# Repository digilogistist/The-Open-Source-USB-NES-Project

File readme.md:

# USB-NES Lite Project Public Release

Brad Taylor  
BTTD Group  
04/05/2023  
https://usbnes.com  

### This is the complete USB-NES Lite 0.08/0.79 production unit engineering archive, containing:

- Source code
- Firmware binaries (composite and discrete)
- PCB engineering files (USB-NES, NES-BACKUP and new NES-FASTGFX)
- Serial wire debug wiring diagram
- Technical documentations
- Quick setup guide print-out
- DIY kit guide print-out (manufacturing instructions)
- Owner's manual PDF
- 3D case models
- Manufacturing BOMs and part source links
- Photo gallery

## Firmware Binaries

Inside the USB-NES is an STM32F103C8 microcontroller running at 72 MHz, which usually includes a very cozy 64 K Bytes of on-board flash memory.  Sometimes as a bonus though, the "Blue Pill" comes with double that amount of storage (and possibly even all the time).  While these differences are normally considered a toss-up on a few innocent chance purchases, the 128 KB flash types (aka incognito 'F103CB ones) are more commonly seen with marketplace Blue Pill system boards at slightly higher price points.

Nowadays, the Blue Pills are not as cheap, available, nor as powerful as newer mini system board offerings on the market, but the first generation blue pills with the through-hole mounted micro-USB port and low-profile reset push button switches are the absolute best types you can still get your hands on, if you're lucky.

Moreover, the main functional USB-NES firmware uses only the first 64 KB of flash, where as units with 128 KB would include a DEMO.NES graphics demonstration ROM that would fit in the bonus 64 KB of flash as additional superfluous brand marketing.  The firmware checks for the classic iNES signature where the DEMO.NES file is allocated on the flash to determine if the file should be created in the USB-NES file system.  Therefore, the DEMO.NES binary allocated there can technically be any defacto .NES image that can fit within the high 64 KB flash of a lucky 128 KB Blue Pill sample.  

|Micro Type  |Flash Location|Size  |Composite Binary Source         |
|:-----------|-------------:|-----:|:-------------------------------|
|STM32F103C8 |0x 0800 0000  | 64 KB|/USB-NES_Lite_0.08-0.79_64K.bin |
|STM32F103CB~|0x 0800 0000  |128 KB|/USB-NES_Lite_0.08-0.79_128K.bin|

~ may also be labelled as a "lucky" 'F103C8 model.  

|Flash section |Flash Location|Size |Discrete Binary Location                   |
|:-------------|-------------:|----:|:------------------------------------------|
|Boot Block   @|0x 0800 0000  | 4 KB|/firmware/boot_block/boot_block.bin        |
|Kernel      ~$|0x 0800 1000  |28 KB|/firmware/kernel/Debug/kernel.bin          |
|Application ^$|0x 0800 8000  |26 KB|/firmware/application/Debug/application.bin|
|SETTINGS.TXT %|0x 0800 E800  | 1 KB|                                           |
|BCMTABLE.BIN  |0x 0800 EC00  | 1 KB|/firmware/BCMTABLE.BIN                     |
|OVERRIDE.BIN  |0x 0800 F000  | 4 KB|/firmware/OVERRIDE.BIN                     |
|DEMO.NES     &|0x 0801 0000  |64 KB|/firmware/DEMO.BIN                         |

~ Uses lower 10 KB of system RAM  
^ Uses upper 10 KB of system RAM  
$ Compiled using Atollic TruStudio (see ./BUILD.BAT for console log)  
% This data is auto-generated by the application firmware  
& DEMO.NES is disabled in SETTINGS.TXT by default  
@ Assembled and output to binary using windy script /firmware/boot_block/BUILD.BAT  

### Flashing the discrete binaries to USB-NES
1. Acquire an ST-LINK Serial Wire Debug programming tool; they are cheap + easy to get.
2. Install the ST-LINK programming utility software.
3. Refer to the /USB-NES-SWD_pinout.jpg for connecting the ST-LINK to USB-NES via SWD.
4. Be sure the USB-NES has its USB port powered when connecting via SWD.
5. Hold in the reset button on USB-NES for a couple of seconds or so, while using the ST-LINK utility to connect to the STM32F103 micro via SWD interface.
6. Deactivate the readout protection on the STM32F103 by unchecking it in the option switches.  Please note this will completely erase the existing contents of the USB-NES firmware.  If the readout protection is not active, you should instead erase the entire contents of the chip by using the utility's Erase command.
7. Load the binary files into the ST-LINK utility~, and program them to the aforementioned corresponding locations in flash memory.  The five critical binaries to flash to USB-NES are the Boot Block, Kernel, Application, BCMTABLE.BIN, and OVERRIDE.BIN.  SETTINGS.TXT is auto-generated by the application, and DEMO.NES is entirely optional (for 128 KB units only).

~ Alternately, the ST-LINK utility command line interface may also be used to flash all five critical binaries automatically; please see /FLASHBALL.BAT for a windy example.

## Source Code

The Kernel and Application projects offered here are built with STM32cubeMX, using the USB FS and mass storage class middlewares provided by ST Microelectronics, which is copywritten code.  Therefore, their source code is provided here strictly under the "fair use" doctrine; no infringement is implied nor intended in its parallel inclusion with this public-domain USB-NES preservation project and related functional source code files.

This default USB layer uses almost all the flash space in the kernel, but probably can be optimized to use less.  Moreover, the STM32cubeMX does not allow the implementation of a USB composite device (such as MSC + HID) on this particular STM32 micro; this is why USB-NES Lite never got NES gamepad socket add-ons over its trial run.  Many on-and-off attempts were made to hack together the two separate STM32 USB functions with no success; it is not clear to me at the time of this writing if the STM32F103C8 has enough flash or RAM resources to employ a USB MSC + HID composite device within the confines of the kernel binary.

The main functional USB-NES source code provided here is located as follows:

|Source type|Language  |Size  |Location                              |
|:----------|:---------|-----:|:-------------------------------------|
|Boot Block |ARM M3 ASM| 13745|/firmware/boot_block/boot_block.s     |
|Kernel     |C         | 25177|/firmware/kernel/Src/usbd_storage_if.c|
|Application|C         |120352|/firmware/application/Src/main.c      |

## PCB Files

Both USB-NES-02 and NES-BACKUP-02 are electrically identical products, and differ only with the Blue Pill/USB port orientation (side vs. back) to their respective PCBs.

The NES-BACKUP-02 PCB predates USB-NES-02, and does not have a nice shell design like for USB-NES Lite.  Note the only feature of this PCB is the 6-pin header that connects to the NES cartridge CIC pins, for easy AVR CIclone boardset programming.  Only 11 NES-BACKUP-01 units are currently known to exist.  Note there is no corner mounting holes, nor is there a footprint for the necessary electrolytic capacitor in this design, which are bugs that need addressing.  The -02 revision fixes a footprint pinout bug present on the -01 models, involving the orientation of the power MOSFET component.

USB-NES-02 is a better follow-up PCB to the aforementioned design, that adds in an experimental mini phone plug for theoretical expansion audio access, and leaves room in the front for further possible expansions like NES gamepad ports and such.  At least 100 USB-NES-01 PCB assemblies are known to exist, and many of these have been assembled into complete USB-NES Lite consumer units.  Note there is no footprint for the necessary electrolytic capacitor in this design, but it is possible to piggy-back solder it onto existing points on the PCB assembly (see /cap_add/ for pix).  A 1.6 mm PCB thickness is strongly recommended for manufacturing USB-NES-02.  All USB-NES firmware binaries mentioned in this document are intended for USB-NES-02.

USB-NES-04 is an enhanced version of the previous design that adds four controller ports to the USB-NES.  There is no firmware that exists yet to take advantage of the enhancements in this hardware design.  Moreover, no PCBs nor related shell designs have yet been manufactured for this either.  More info here:  
https://youtu.be/dRpi10Yrjks

NES-FASTGFX-01 is a completely original concept NES cart mapper (1.2 mm thick) PCB design made for new NES game development.  A complete manufacturing BOM + working (as of 04-13-2023) parts source list for NES-FASTGFX-01 can be found in "/PCB (NES-FASTGFX-01)/BOM-FASTGFX.ods"

### NES-FASTGFX-01 Specs
- 512 K byte PRG flash (SST39SF040)
- 32 K byte PRG-RAM
- 512 K byte CHR-RAM
- 32768 playfield tiles (@ PPU $0000-$0FFF)
- 4 PPU mirroring modes
- 16-bit VBLANK time stamp counter
- 128 sprite banks (@ PPU $1000-$1FFF)
- HI name table located in first 2 KB of CHR-RAM
- 4-CPU clock cycle CHR-RAM byte filling @ PPU $2000-$3EFF~
- ATMEL ATtiny13A CIClone twin footprint (through-hole & SMT)

~ CPU writes to PPU data I/O register $2xx7/$3xx7, will write the encoded 8-bit xx value to the CHR-RAM in one single STA/STX/STY abs. 6502 instruction.  In this case, writes to PPU $2000-$2FFF memory will fill the HI name tables with the xx value (and internal 2 KB LO NT as per usual CPU data), while writes to PPU $3000-$3EFF will write xx to the selected CHR-RAM sprite bank (meanwhile disabling the LO NT).  The CHR-RAM may also be disabled during name table fills, when updating only the LO NT is desired.   Moreover, the CHR-RAM may also be bi-directionally accessed via the traditional CPU $2007 data I/O port @ PPU $1000-$1FFF memory, swapping in the selected 4 KB sprite bank there as well.  PPU bank $0000-$0FFF is only used for playfield rendering; it can just be ignored otherwise.

The most notable feature of this mapper is the expansion of the original 8-bit name table tile codes to 15-bits; this is made possible by using a private graphics data bus in the cartridge for handling the NT HI business during a NT fetch phase.  Moreover, the NT fetch phase is identified as a read cycle from PPU $2000-$3FFF that follows a read from PPU $0000-$1FFF; this corresponds to how the PPU fetches CHR memory during on-screen playfield rendering.  The NT HI byte is then fetched from the first 2KB of CHR-RAM (using the identical mirroring scheme the NES internal 2K VRAM is configured for), and is stored in a register.  The register is then used as the basis for the 4KB bank selection for pattern graphics access @ PPU $0000-$0FFF, which is where the PPU should be normally configured to allocate the 4KB playfield graphics bank.

The VBLANK time stamp counter is reset from any reads from the PPU, so once screen rendering is done, this counter will start to count up every CPU clock.  Consequently, the 16-bit value read here can indicate how far the PPU is in VBLANK or the frame render period, relative to the CPU NMI event (or thereabouts).  If your VBLANK code runs past the 20-scanline (NTSC) limit, the time stamp counter can be used as the basis for forming the correct PPU scroll programming values, based on how many scanlines the render has advanced into the visible frame.  Reading the LO byte of the time stamp count register latches the next LO and HI 8-bit time stamp count samples to be read back.  Therefore, it is possible to only just read the LO TSC register when measuring CPU clock counts of less than 256 clocks.

When using FASTGFX for NES game development, writing to PPU memory is up to 50% faster, and VBLANK code time may be extended dynamically past the on-screen cutoff point, all while having access to a serious amount of graphical tiles for use with both backgrounds and sprites.

### Flash Cart Story
NES-FASTGFX-01 is the answer to a previous programmable NES cart production attempt I made back in 2018: "NES-RED-PILL-02". This older design was more complicated due to the presence of both CHR-RAM and CHR-flash, where the PPU architecture is split into separate sections for sprites (RAM) and playfield tiles (flash/RAM).  The idea was to have 512 KB of CHR-flash for background tiles, and 32 KB CHR-RAM for sprites + BG, but the hardware required to implement the 16-bit background tile index code extensions ended up making programming the CHR-flash chip a complex nightmare.

This was also my first attempt implementing 5-volt flash chips into a new NES cart design.  One critical detail about using flash chips for PRG memory versus SRAM is the requirement of an inverted read/write line for the /OE input on the chip, which would normally just be tied to ground for a typical SRAM implementation.

My long-term plan was to develop game software for the NES using these cart boards, while using NES-BACKUP/USB-NES as the main flashing/programming tool, providing an easy-to-use drag + drop user interface.  These boards have a lot of SMD parts on them, so I got ten of them manufactured and populated professionally, which also made this cart production really expensive.

Subsequently however, once I had built NES-BACKUP and started testing out the NES-RED-PILL boards, I found out I made some fatal design mistakes on the boards.  Most notably, I discovered that both CHR and PRG flash chips could not be programmed efficiently or even at all, without reworking the boards and adding another chip!  After eventually reworking one board, I did manage to get the PRG + CHR flashing to work with USB-NES, but when programming the CHR-flash there was always 4KB in the last bank on the chip that would not flash correctly.  I couldn't figure out what the source of the CHR-flash corruption was, and lost my nerve.  From there on (late 2019), I focused on developing the USB-NES firmware, since I was at a loss with my game boards.

Then three years later, I reworked a second NES-RED-PILL board to discover that the CHR-flash on the first board was actually fried.  Apparently, all the initial testing I was doing on these boards before reworking them was enough to cause the CHR-flash chip on one board to partially self-destruct, and cause it to always fail a full flash memory programming test.  But now, the second reworked board was flashing perfectly using USB-NES!  So now I know what I did wrong, and how to do it right this time.

I took everything I learned from that first costly and disappointing NES-RED-PILL production disaster, trimmed the fat and tweaked the ideas, and made NES-FASTGFX: a state-of-the-art, open-source, graphics expansion NES development cartridge boardset PCB design, that adds powerful extensions to the NES architecture with a simplified programming environment, using a handful of easy-to-source boardset parts.

USB-NES support for NES-FASTGFX boardset development with full drag + drop PRG-flashing is speculated down the road, using existing methods in the USB-NES source code that have been 100% tested and confirmed working on reworked NES-RED-PILL-02 flash boards.  More info on the NES-RED-PILL can be seen here:

https://youtu.be/C34mVn180Tk  
https://youtu.be/JX10NZo6VX4

## USB-NES Lite BOM

/BOM-final_USB-NES_Lite_2021.ods

This bill of materials includes everything to make a production USB-NES Lite system, with a working (as of 04-13-2023) part source list.

The 3D models are typically printed via 1.75/0.4 mm filament/nozzle 3D printer with 5% infill, 0.2 mm layers, and 1.2 mm top/bottom thickness.

The PCB files were made with Kicad.

Do not assemble before reading the manufacturing instructions.

## Manufacturing Instructions

The step-by-step assembly guide for building USB-NES Lite is contained in:  
/USB-NES DIY KIT (p.1).pdf  
/USB-NES DIY KIT (p.2).pdf  
https://usbnes.com/usb-nes-lite-diy-kit/  

The companion video can be found here (doesn't cover adding the capacitor):  
https://youtu.be/VL_1Z1ONgns  

The capacitor install guide here:  
/cap_add/  
https://usbnes.com/power-system-upgrade/

## Thank-Yous

All the USB-NES Lite project supporters  
The entire NES emulation dev scene  
Generational Gamer  
Paul Belanger  
Thor Robinson  
Troy Denton  
Henry Hoy  
Wolf  
Loopy  
Disch  
Dwedit  
Blarrg  
nocash  
Tepples  
Kevtris  
Bootgod  
Bregalad  
Bananmos  
Tokumaru  
Lidnariq  
Ulfalizer  
Rainwarrior  
infiniteneslives  
beannaich  
Quietust  
Memblers  
jeffqchen  
NEScartDB  
NESDEV wiki  
Eugene's blog  
ST Microelectronics  
Nintendo of America, Inc. (and NCL of Japan, too)  
And of course, the reader  

## License

Copywritten works, such as technical manuals and source code included in this repository are for educational and preservational "fair use" purposes only.  No copyright infringement is implied, solicited nor intended with the inclusion of these copywritten works for the Open-Source USB-NES Project.

The rest of the work in this archive, including any BTTD Group or Brad Taylor properties, is licensed under a Creative Commons Attribution-ShareAlike 4.0 International License.

http://creativecommons.org/licenses/by-sa/4.0/

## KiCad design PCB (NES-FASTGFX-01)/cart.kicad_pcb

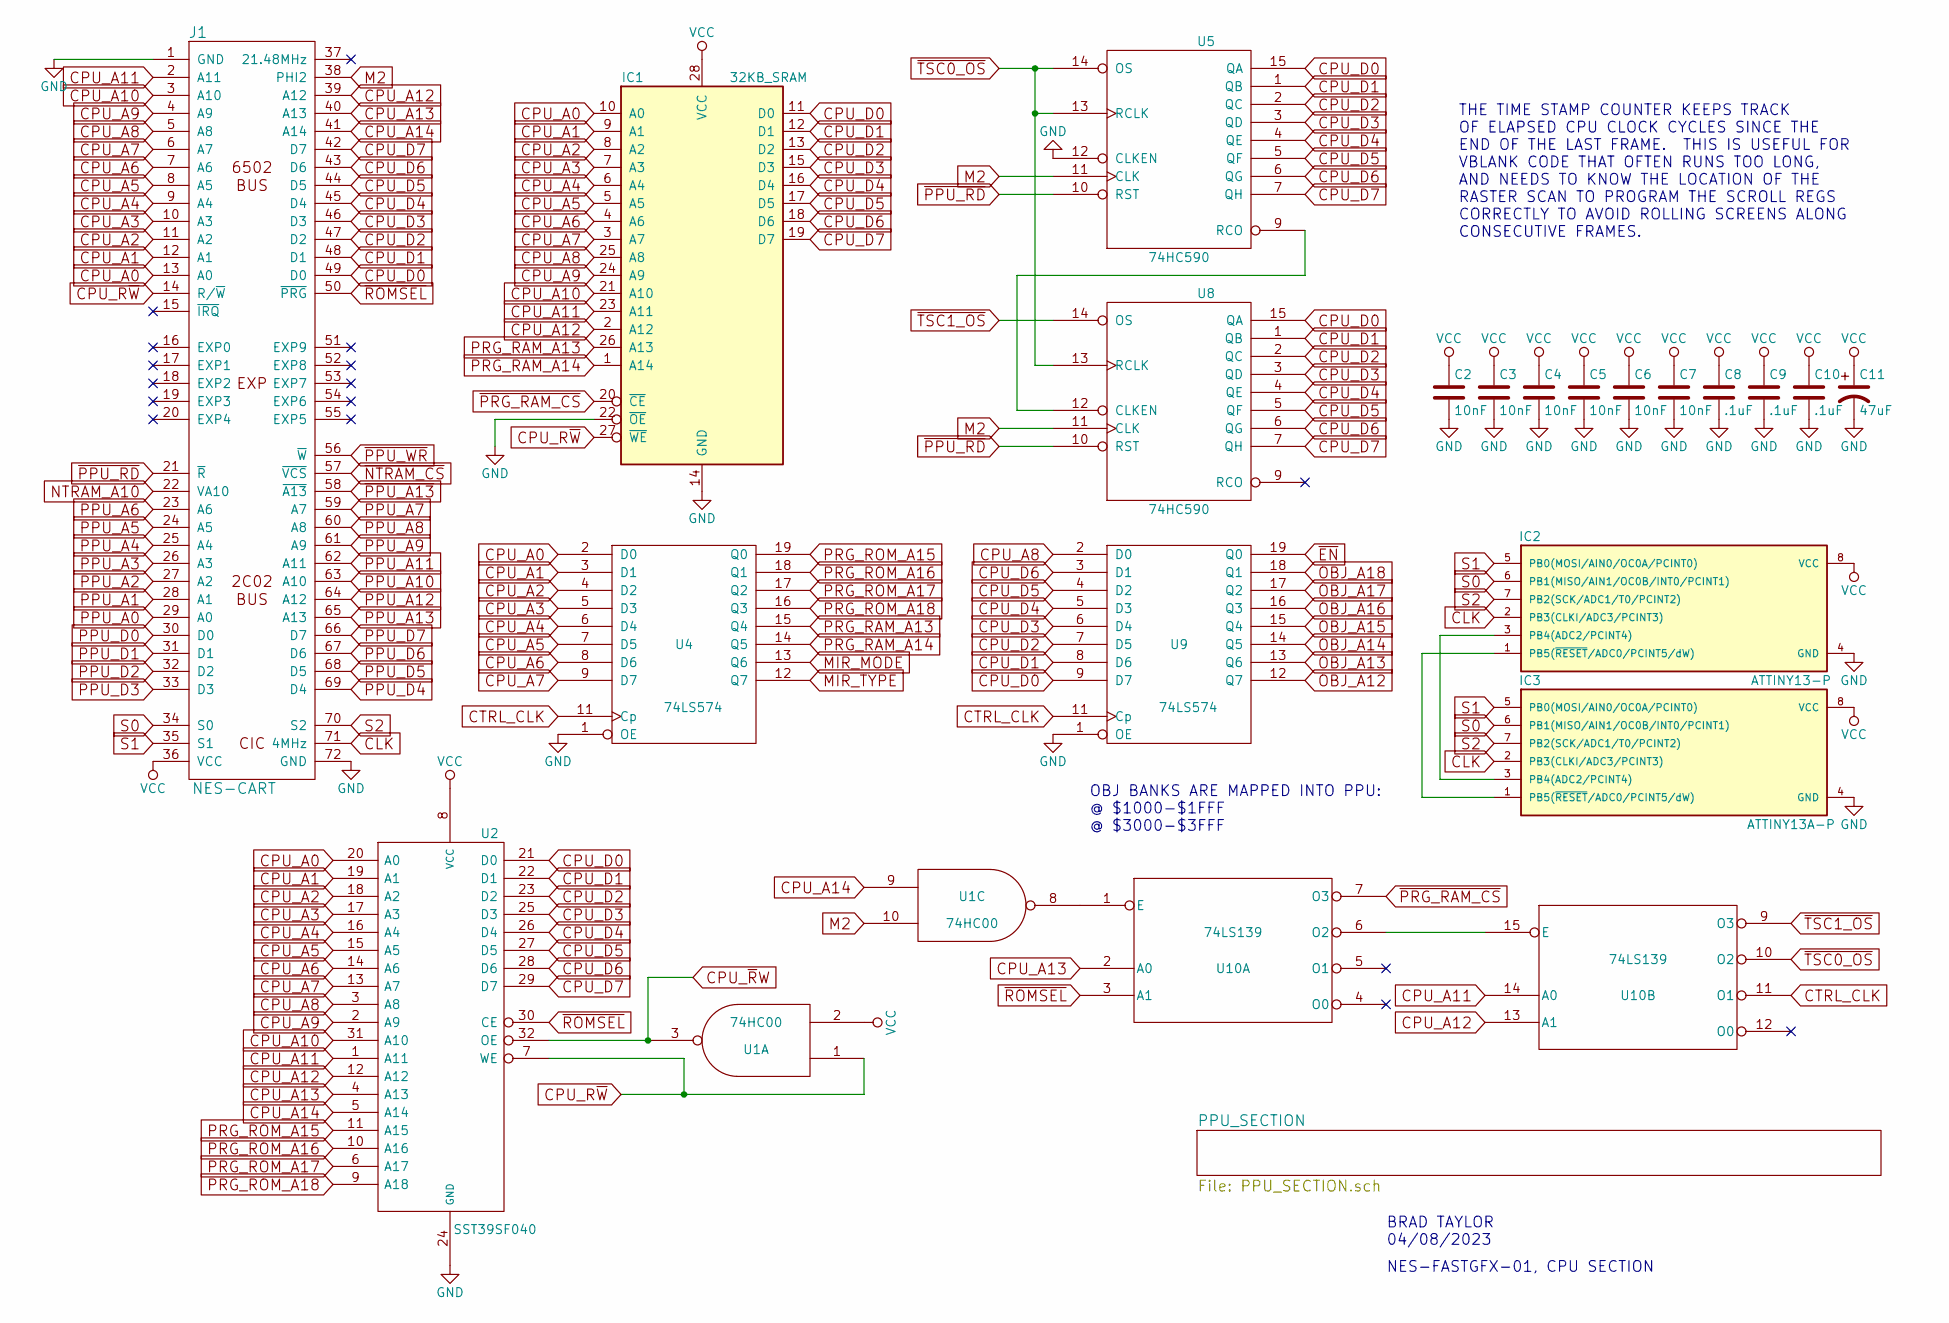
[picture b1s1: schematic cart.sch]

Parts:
C2, C3, C4, C5, C6, C7: 10nF; C_0603_1608Metric_Pad1.05x0.95mm_HandSolder
C8, C9, C10: .1uF; C_0603_1608Metric_Pad1.05x0.95mm_HandSolder
C11: 47uF; CP_Elec_4x5.3
IC1: 32KB_SRAM; SOIC-28
IC2: ATTINY13-P; DIP-8_W7.62mm
IC3: ATTINY13A-P; SOIC-8_3.9x4.9mm_P1.27mm
J1: NES-CART; NES_CART_FINGERS
U1: 74HC00; TSSOP-14_4.4x5mm_P0.65mm
U2: SST39SF040; SOIC-32
U4, U9: 74LS574; TSSOP-20_4.4x6.5mm_P0.65mm
U5, U8: 74HC590; TSSOP-16_4.4x5mm_P0.65mm
U10: 74LS139; TSSOP-16_4.4x5mm_P0.65mm

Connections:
CLK: IC2.2 (PB3(CLKI/ADC3/PCINT3)), IC3.2 (PB3(CLKI/ADC3/PCINT3)), J1.71 (4MHz)
CPU_A0: IC1.10 (A0), J1.13 (A0), U2.20 (A0), U4.2 (D0)
CPU_A1: IC1.9 (A1), J1.12 (A1), U2.19 (A1), U4.3 (D1)
CPU_A2: IC1.8 (A2), J1.11 (A2), U2.18 (A2), U4.4 (D2)
CPU_A3: IC1.7 (A3), J1.10 (A3), U2.17 (A3), U4.5 (D3)
CPU_A4: IC1.6 (A4), J1.9 (A4), U2.16 (A4), U4.6 (D4); also elsewhere on the board
CPU_A5: IC1.5 (A5), J1.8 (A5), U2.15 (A5), U4.7 (D5); also elsewhere on the board
CPU_A6: IC1.4 (A6), J1.7 (A6), U2.14 (A6), U4.8 (D6); also elsewhere on the board
CPU_A7: IC1.3 (A7), J1.6 (A7), U2.13 (A7), U4.9 (D7); also elsewhere on the board
CPU_A8: IC1.25 (A8), J1.5 (A8), U2.3 (A8), U9.2 (D0); also elsewhere on the board
CPU_A9: IC1.24 (A9), J1.4 (A9), U2.2 (A9); also elsewhere on the board
CPU_A10: IC1.21 (A10), J1.3 (A10), U2.31 (A10); also elsewhere on the board
CPU_A11: IC1.23 (A11), J1.2 (A11), U2.1 (A11), U10.14 (A0); also elsewhere on the board
CPU_A12: IC1.2 (A12), J1.39 (A12), U2.12 (A12), U10.13 (A1)
CPU_A13: J1.40 (A13), U2.4 (A13), U10.2 (A0)
CPU_A14: J1.41 (A14), U1.9, U2.5 (A14)
CPU_D0: IC1.11 (D0), J1.49 (D0), U2.21 (D0), U5.15 (QA), U8.15 (QA), U9.9 (D7)
CPU_D1: IC1.12 (D1), J1.48 (D1), U2.22 (D1), U5.1 (QB), U8.1 (QB), U9.8 (D6)
CPU_D2: IC1.13 (D2), J1.47 (D2), U2.23 (D2), U5.2 (QC), U8.2 (QC), U9.7 (D5)
CPU_D3: IC1.15 (D3), J1.46 (D3), U2.25 (D3), U5.3 (QD), U8.3 (QD), U9.6 (D4)
CPU_D4: IC1.16 (D4), J1.45 (D4), U2.26 (D4), U5.4 (QE), U8.4 (QE), U9.5 (D3)
CPU_D5: IC1.17 (D5), J1.44 (D5), U2.27 (D5), U5.5 (QF), U8.5 (QF), U9.4 (D2)
CPU_D6: IC1.18 (D6), J1.43 (D6), U2.28 (D6), U5.6 (QG), U8.6 (QG), U9.3 (D1)
CPU_D7: IC1.19 (D7), J1.42 (D7), U2.29 (D7), U5.7 (QH), U8.7 (QH)
CPU_R~W: IC1.27 (~WE~), J1.14 (R/~W), U1.1, U2.7 (WE)
CPU_~R~W: U1.3, U2.32 (OE); also elsewhere on the board
CTRL_CLK: U4.11 (Cp), U9.11 (Cp), U10.11 (O1)
GND: C2.2, C3.2, C4.2, C5.2, C6.2, C7.2, C8.2, C9.2, C10.2, C11.2, IC1.14 (GND), IC1.22 (~OE~), IC2.4 (GND), IC3.4 (GND), J1.1 (GND), J1.72 (GND), U1.7 (GND), U2.24 (GND), U4.1 (OE), U4.10 (GND), U5.8 (GND), U5.12 (CLKEN), U8.8 (GND), U9.1 (OE), U9.10 (GND), U10.8 (GND); also elsewhere on the board
M2: J1.38 (PHI2), U1.10, U5.11 (CLK), U8.11 (CLK); also elsewhere on the board
MIR_MODE: U4.13 (Q6); also elsewhere on the board
MIR_TYPE: U4.12 (Q7); also elsewhere on the board
NTRAM_A10: J1.22 (VA10); also elsewhere on the board
unnamed: IC2.1 (PB5(~RESET~/ADC0/PCINT5/dW)), IC3.1 (PB5(~RESET~/ADC0/PCINT5/dW))
unnamed: IC2.3 (PB4(ADC2/PCINT4)), IC3.3 (PB4(ADC2/PCINT4))
unnamed: U1.8, U10.1 (E)
unnamed: U5.9 (RCO), U8.12 (CLKEN)
unnamed: U10.6 (O2), U10.15 (E)
OBJ_A12: U9.12 (Q7); also elsewhere on the board
OBJ_A13: U9.13 (Q6); also elsewhere on the board
OBJ_A14: U9.14 (Q5); also elsewhere on the board
OBJ_A15: U9.15 (Q4); also elsewhere on the board
OBJ_A16: U9.16 (Q3); also elsewhere on the board
OBJ_A17: U9.17 (Q2); also elsewhere on the board
OBJ_A18: U9.18 (Q1); also elsewhere on the board
PPU_A0: J1.29 (A0); also elsewhere on the board
PPU_A1: J1.28 (A1); also elsewhere on the board
PPU_A2: J1.27 (A2); also elsewhere on the board
PPU_A3: J1.26 (A3); also elsewhere on the board
PPU_A4: J1.25 (A4); also elsewhere on the board
PPU_A5: J1.24 (A5); also elsewhere on the board
PPU_A6: J1.23 (A6); also elsewhere on the board
PPU_A7: J1.59 (A7); also elsewhere on the board
PPU_A8: J1.60 (A8); also elsewhere on the board
PPU_A9: J1.61 (A9); also elsewhere on the board
PPU_A10: J1.63 (A10); also elsewhere on the board
PPU_A11: J1.62 (A11); also elsewhere on the board
PPU_A12: J1.64 (A12); also elsewhere on the board
PPU_A13: J1.65 (A13); also elsewhere on the board
PPU_D0: J1.30 (D0); also elsewhere on the board
PPU_D1: J1.31 (D1); also elsewhere on the board
PPU_D2: J1.32 (D2); also elsewhere on the board
PPU_D3: J1.33 (D3); also elsewhere on the board
PPU_D4: J1.69 (D4); also elsewhere on the board
PPU_D5: J1.68 (D5); also elsewhere on the board
PPU_D6: J1.67 (D6); also elsewhere on the board
PPU_D7: J1.66 (D7); also elsewhere on the board
PRG_RAM_A13: IC1.26 (A13), U4.15 (Q4)
PRG_RAM_A14: IC1.1 (A14), U4.14 (Q5)
PRG_ROM_A15: U2.11 (A15), U4.19 (Q0)
PRG_ROM_A16: U2.10 (A16), U4.18 (Q1)
PRG_ROM_A17: U2.6 (A17), U4.17 (Q2)
PRG_ROM_A18: U2.9 (A18), U4.16 (Q3)
S0: IC2.6 (PB1(MISO/AIN1/OC0B/INT0/PCINT1)), IC3.6 (PB1(MISO/AIN1/OC0B/INT0/PCINT1)), J1.34 (S0)
S1: IC2.5 (PB0(MOSI/AIN0/OC0A/PCINT0)), IC3.5 (PB0(MOSI/AIN0/OC0A/PCINT0)), J1.35 (S1)
S2: IC2.7 (PB2(SCK/ADC1/T0/PCINT2)), IC3.7 (PB2(SCK/ADC1/T0/PCINT2)), J1.70 (S2)
VCC: C2.1, C3.1, C4.1, C5.1, C6.1, C7.1, C8.1, C9.1, C10.1, C11.1, IC1.28 (VCC), IC2.8 (VCC), IC3.8 (VCC), J1.36 (VCC), U1.2, U1.14 (VCC), U2.8 (VCC), U4.20 (VCC), U5.16 (VCC), U8.16 (VCC), U9.20 (VCC), U10.16 (VCC); also elsewhere on the board
~EN: U9.19 (Q0); also elsewhere on the board
~NTRAM_CS: J1.57 (~VCS); also elsewhere on the board
~PPU_A13: J1.58 (~A13); also elsewhere on the board
~PPU_RD: J1.21 (~R), U5.10 (RST), U8.10 (RST); also elsewhere on the board
~PPU_WR: J1.56 (~W); also elsewhere on the board
~PRG_RAM_CS: IC1.20 (~CE~), U10.7 (O3)
~ROMSEL: J1.50 (~PRG), U2.30 (CE), U10.3 (A1)
~TSC0_OS: U5.13 (RCLK), U5.14 (OS), U8.13 (RCLK), U10.10 (O2)
~TSC1_OS: U8.14 (OS), U10.9 (O3)

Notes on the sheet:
NES-FASTGFX-01, CPU SECTION
BRAD TAYLOR 04/08/2023
OBJ BANKS ARE MAPPED INTO PPU: @ $1000-$1FFF @ $3000-$3FFF
THE TIME STAMP COUNTER KEEPS TRACK OF ELAPSED CPU CLOCK CYCLES SINCE THE END OF THE LAST FRAME. THIS IS USEFUL FOR VBLANK CODE THAT OFTEN RUNS TOO LONG, AND NEEDS TO KNOW THE LOCATION OF THE RASTER SCAN TO PROGRAM THE SCROLL REGS CORRECTLY TO AVOID ROLLING SCREENS ALONG CONSECUTIVE FRAMES.

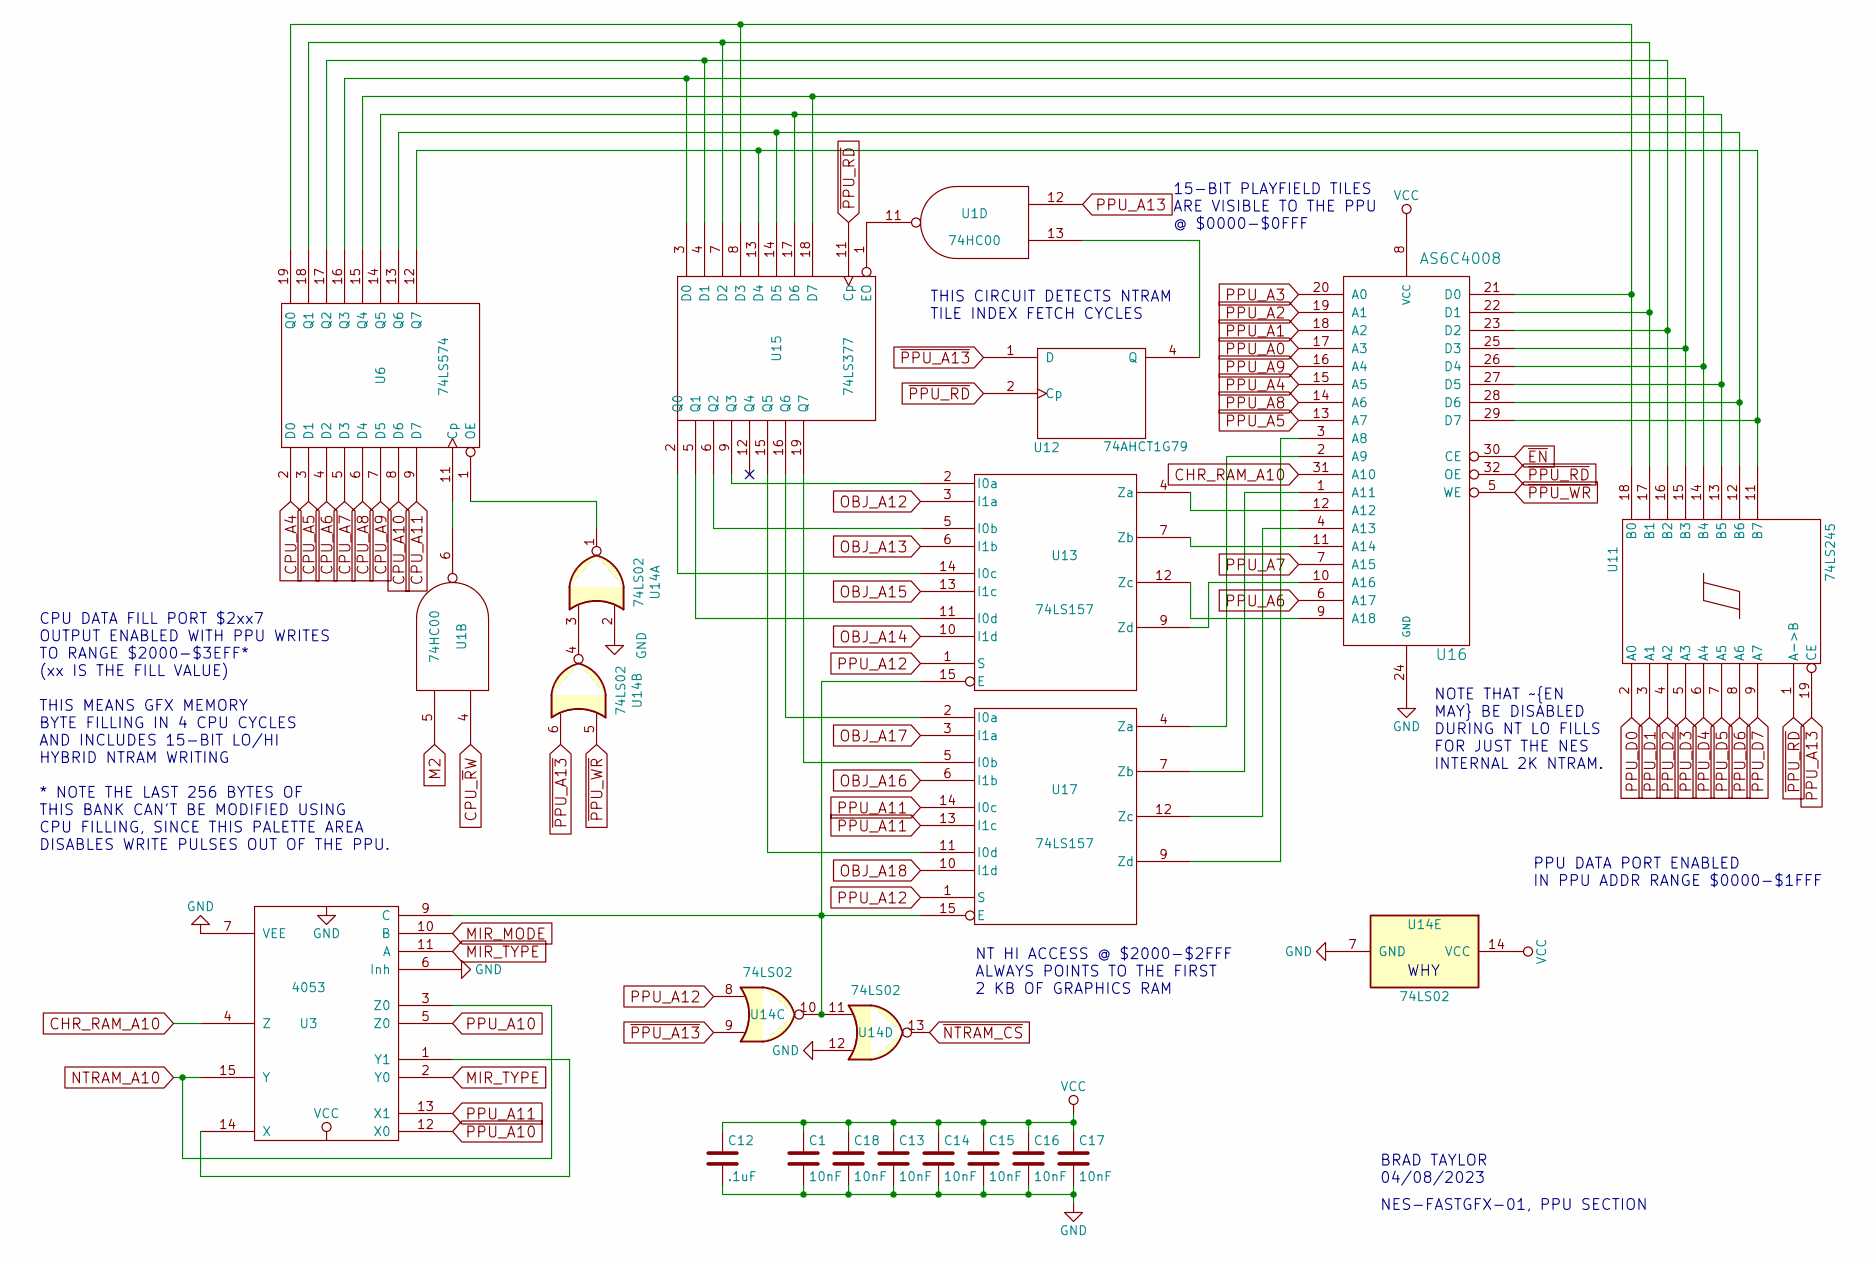
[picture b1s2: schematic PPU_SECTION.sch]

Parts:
C1, C13, C14, C15, C16, C17, C18: 10nF; C_0603_1608Metric_Pad1.05x0.95mm_HandSolder
C12: .1uF; C_0603_1608Metric_Pad1.05x0.95mm_HandSolder
U1: 74HC00; TSSOP-14_4.4x5mm_P0.65mm
U3: 4053; TSSOP-16_4.4x5mm_P0.65mm
U6: 74LS574; TSSOP-20_4.4x6.5mm_P0.65mm
U11: 74LS245; TSSOP-20_4.4x6.5mm_P0.65mm
U12: 74AHCT1G79; SOT-353_SC-70-5
U13, U17: 74LS157; TSSOP-16_4.4x5mm_P0.65mm
U14: 74LS02; TSSOP-14_4.4x5mm_P0.65mm
U15: 74LS377; TSSOP-20_4.4x6.5mm_P0.65mm
U16: AS6C4008; SOIC-32

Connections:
CHR_RAM_A10: U3.4 (Z), U16.31 (A10)
CPU_A4: U6.2 (D0); also elsewhere on the board
CPU_A5: U6.3 (D1); also elsewhere on the board
CPU_A6: U6.4 (D2); also elsewhere on the board
CPU_A7: U6.5 (D3); also elsewhere on the board
CPU_A8: U6.6 (D4); also elsewhere on the board
CPU_A9: U6.7 (D5); also elsewhere on the board
CPU_A10: U6.8 (D6); also elsewhere on the board
CPU_A11: U6.9 (D7); also elsewhere on the board
CPU_~R~W: U1.4; also elsewhere on the board
GND: C1.2, C12.2, C13.2, C14.2, C15.2, C16.2, C17.2, C18.2, U1.7 (GND), U3.6 (Inh), U3.7 (VEE), U3.8 (VSS), U6.10 (GND), U11.10 (GND), U12.3 (GND), U13.8 (GND), U14.2, U14.7 (GND), U14.12, U15.10 (GND), U16.24 (GND), U17.8 (GND); also elsewhere on the board
M2: U1.5; also elsewhere on the board
MIR_MODE: U3.10 (B); also elsewhere on the board
MIR_TYPE: U3.2 (Y0), U3.11 (A); also elsewhere on the board
NTRAM_A10: U3.3 (Z0), U3.15 (Y); also elsewhere on the board
unnamed: U1.6, U6.11 (Cp)
unnamed: U1.11, U15.1 (EO)
unnamed: U1.13, U12.4 (Q)
unnamed: U3.1 (Y1), U3.14 (X)
unnamed: U6.12 (Q7), U11.11 (B7), U15.13 (D4), U16.29 (D7)
unnamed: U6.13 (Q6), U11.12 (B6), U15.14 (D5), U16.28 (D6)
unnamed: U6.14 (Q5), U11.13 (B5), U15.17 (D6), U16.27 (D5)
unnamed: U6.15 (Q4), U11.14 (B4), U15.18 (D7), U16.26 (D4)
unnamed: U6.16 (Q3), U11.15 (B3), U15.3 (D0), U16.25 (D3)
unnamed: U6.17 (Q2), U11.16 (B2), U15.4 (D1), U16.23 (D2)
unnamed: U6.18 (Q1), U11.17 (B1), U15.7 (D2), U16.22 (D1)
unnamed: U6.19 (Q0), U11.18 (B0), U15.8 (D3), U16.21 (D0)
unnamed: U13.2 (I0a), U15.9 (Q3)
unnamed: U13.4 (Za), U16.12 (A12)
unnamed: U13.5 (I0b), U15.6 (Q2)
unnamed: U13.7 (Zb), U16.11 (A14)
unnamed: U13.9 (Zd), U16.10 (A16)
unnamed: U13.11 (I0d), U15.5 (Q1)
unnamed: U13.12 (Zc), U16.9 (A18)
unnamed: U13.14 (I0c), U15.2 (Q0)
unnamed: U3.9 (C), U13.15 (E), U14.10, U14.11, U17.15 (E)
unnamed: U6.1 (OE), U14.1
unnamed: U14.3, U14.4
unnamed: U15.15 (Q5), U17.11 (I0d)
unnamed: U15.16 (Q6), U17.2 (I0a)
unnamed: U15.19 (Q7), U17.5 (I0b)
unnamed: U16.1 (A11), U17.7 (Zb)
unnamed: U16.2 (A9), U17.4 (Za)
unnamed: U16.3 (A8), U17.9 (Zd)
unnamed: U16.4 (A13), U17.12 (Zc)
OBJ_A12: U13.3 (I1a); also elsewhere on the board
OBJ_A13: U13.6 (I1b); also elsewhere on the board
OBJ_A14: U13.10 (I1d); also elsewhere on the board
OBJ_A15: U13.13 (I1c); also elsewhere on the board
OBJ_A16: U17.6 (I1b); also elsewhere on the board
OBJ_A17: U17.3 (I1a); also elsewhere on the board
OBJ_A18: U17.10 (I1d); also elsewhere on the board
PPU_A0: U16.17 (A3); also elsewhere on the board
PPU_A1: U16.18 (A2); also elsewhere on the board
PPU_A2: U16.19 (A1); also elsewhere on the board
PPU_A3: U16.20 (A0); also elsewhere on the board
PPU_A4: U16.15 (A5); also elsewhere on the board
PPU_A5: U16.13 (A7); also elsewhere on the board
PPU_A6: U16.6 (A17); also elsewhere on the board
PPU_A7: U16.7 (A15); also elsewhere on the board
PPU_A8: U16.14 (A6); also elsewhere on the board
PPU_A9: U16.16 (A4); also elsewhere on the board
PPU_A10: U3.5 (Z0), U3.12 (X0); also elsewhere on the board
PPU_A11: U3.13 (X1), U17.13 (I1c), U17.14 (I0c); also elsewhere on the board
PPU_A12: U13.1 (S), U14.8, U17.1 (S); also elsewhere on the board
PPU_A13: U1.12, U11.19 (CE); also elsewhere on the board
PPU_D0: U11.2 (A0); also elsewhere on the board
PPU_D1: U11.3 (A1); also elsewhere on the board
PPU_D2: U11.4 (A2); also elsewhere on the board
PPU_D3: U11.5 (A3); also elsewhere on the board
PPU_D4: U11.6 (A4); also elsewhere on the board
PPU_D5: U11.7 (A5); also elsewhere on the board
PPU_D6: U11.8 (A6); also elsewhere on the board
PPU_D7: U11.9 (A7); also elsewhere on the board
VCC: C1.1, C12.1, C13.1, C14.1, C15.1, C16.1, C17.1, C18.1, U1.14 (VCC), U3.16 (VDD), U6.20 (VCC), U11.20 (VCC), U12.5 (VCC), U13.16 (VCC), U14.14 (VCC), U15.20 (VCC), U16.8 (VCC), U17.16 (VCC); also elsewhere on the board
~EN: U16.30 (CE); also elsewhere on the board
~NTRAM_CS: U14.13; also elsewhere on the board
~PPU_A13: U12.1 (D), U14.6, U14.9; also elsewhere on the board
~PPU_RD: U11.1 (A->B), U12.2 (Cp), U15.11 (Cp), U16.32 (OE); also elsewhere on the board
~PPU_WR: U14.5, U16.5 (WE); also elsewhere on the board

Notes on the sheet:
BRAD TAYLOR 04/08/2023
PPU DATA PORT ENABLED IN PPU ADDR RANGE $0000-$1FFF
CPU DATA FILL PORT $2xx7 OUTPUT ENABLED WITH PPU WRITES TO RANGE $2000-$3EFF* (xx IS THE FILL VALUE) THIS MEANS GFX MEMORY BYTE FILLING IN 4 CPU CYCLES AND INCLUDES 15-BIT LO/HI HYBRID NTRAM WRITING * NOTE THE LAST 256 BYTES OF THIS BANK CAN'T BE MODIFIED USING CPU FILLING, SINCE THIS PALETTE AREA 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
NES-FASTGFX-01, PPU SECTION
NT HI ACCESS @ $2000-$2FFF ALWAYS POINTS TO THE FIRST 2 KB OF GRAPHICS RAM
15-BIT PLAYFIELD TILES ARE VISIBLE TO THE PPU @ $0000-$0FFF
NOTE THAT ~EN MAY BE DISABLED DURING NT LO FILLS FOR JUST THE NES INTERNAL 2K NTRAM.
THIS CIRCUIT DETECTS NTRAM TILE INDEX FETCH CYCLES
WHY

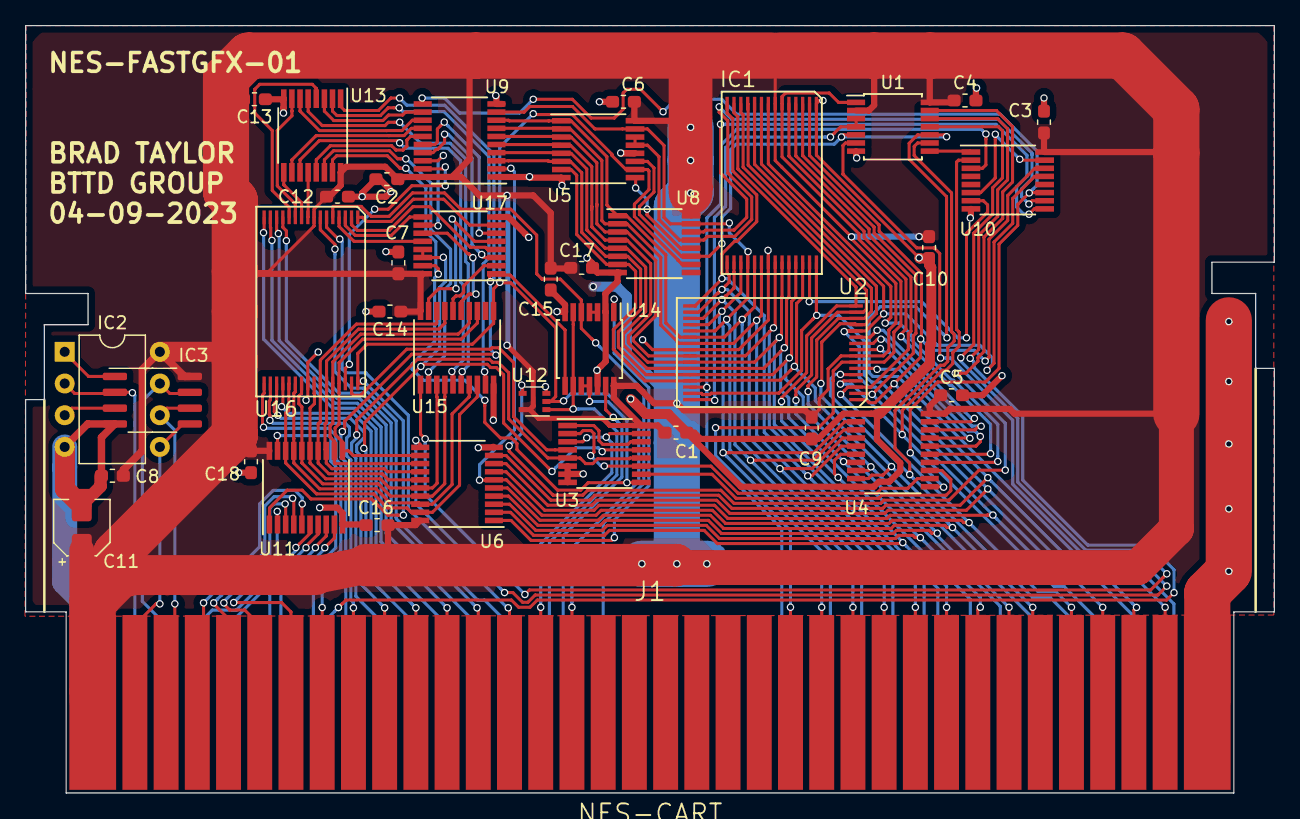
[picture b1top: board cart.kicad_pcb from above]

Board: 2 copper layers, 100.0 x 61.4 mm, 38 parts (0 on the bottom side), 116 nets.

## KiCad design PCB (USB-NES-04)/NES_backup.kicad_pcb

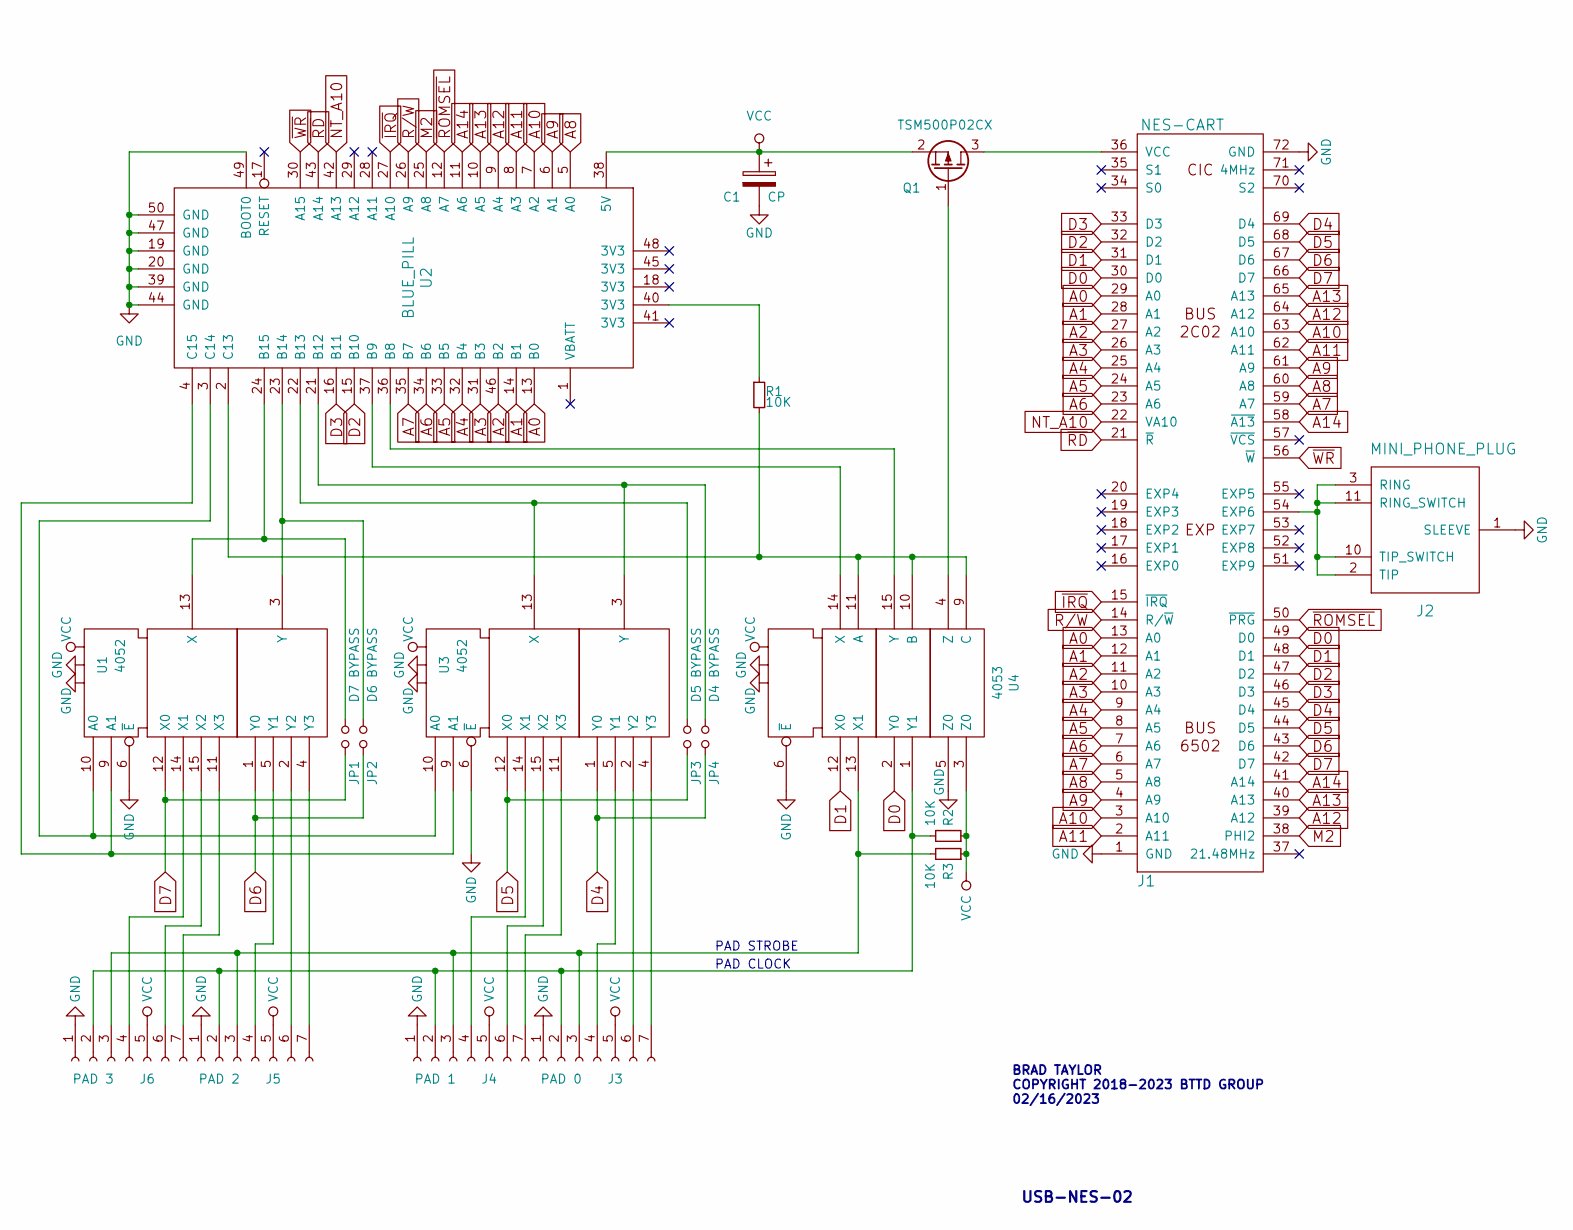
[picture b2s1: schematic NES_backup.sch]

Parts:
C1: CP; CP_Radial_D8.0mm_P3.50mm
J1: NES-CART; NES_CART
J2: MINI_PHONE_PLUG
J3: PAD 0; NES_pad_plug
J4: PAD 1; NES_pad_plug
J5: PAD 2; NES_pad_plug
J6: PAD 3; NES_pad_plug
JP1: D7 BYPASS; SolderJumper-2_P1.3mm_Open_TrianglePad1.0x1.5mm
JP2: D6 BYPASS; SolderJumper-2_P1.3mm_Open_TrianglePad1.0x1.5mm
JP3: D5 BYPASS; SolderJumper-2_P1.3mm_Open_TrianglePad1.0x1.5mm
JP4: D4 BYPASS; SolderJumper-2_P1.3mm_Open_TrianglePad1.0x1.5mm
Q1: TSM500P02CX; SOT-23
R1, R2, R3: 10K; R_1206_3216Metric_Pad1.42x1.75mm_HandSolder
U1, U3: 4052; TSSOP-16_4.4x5mm_P0.65mm
U2: BLUE_PILL; blue_pill
U4: 4053; TSSOP-16_4.4x5mm_P0.65mm

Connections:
A0: J1.13 (A0), J1.29 (A0), U2.13 (B0)
A1: J1.12 (A1), J1.28 (A1), U2.14 (B1)
A2: J1.11 (A2), J1.27 (A2), U2.46 (B2)
A3: J1.10 (A3), J1.26 (A3), U2.31 (B3)
A4: J1.9 (A4), J1.25 (A4), U2.32 (B4)
A5: J1.8 (A5), J1.24 (A5), U2.33 (B5)
A6: J1.7 (A6), J1.23 (A6), U2.34 (B6)
A7: J1.6 (A7), J1.59 (A7), U2.35 (B7)
A8: J1.5 (A8), J1.60 (A8), U2.5 (A0)
A9: J1.4 (A9), J1.61 (A9), U2.6 (A1)
A10: J1.3 (A10), J1.63 (A10), U2.7 (A2)
A11: J1.2 (A11), J1.62 (A11), U2.8 (A3)
A12: J1.39 (A12), J1.64 (A12), U2.9 (A4)
A13: J1.40 (A13), J1.65 (A13), U2.10 (A5)
A14: J1.41 (A14), J1.58 (~A13), U2.11 (A6)
D0: J1.30 (D0), J1.49 (D0), U4.2 (Y0)
D1: J1.31 (D1), J1.48 (D1), U4.12 (X0)
D2: J1.32 (D2), J1.47 (D2), U2.15 (B10)
D3: J1.33 (D3), J1.46 (D3), U2.16 (B11)
D4: J1.45 (D4), J1.69 (D4), JP4.1, U3.1 (Y0)
D5: J1.44 (D5), J1.68 (D5), JP3.1, U3.12 (X0)
D6: J1.43 (D6), J1.67 (D6), JP2.1, U1.1 (Y0)
D7: J1.42 (D7), J1.66 (D7), JP1.1, U1.12 (X0)
GND: C1.2, J1.1 (GND), J1.72 (GND), J2.1 (SLEEVE), J3.1, J4.1, J5.1, J6.1, U1.6 (~E), U1.7 (VEE), U1.8 (Vss), U2.19 (GND), U2.20 (GND), U2.39 (GND), U2.44 (GND), U2.47 (GND), U2.49 (BOOT0), U2.50 (GND), U3.6 (~E), U3.7 (VEE), U3.8 (Vss), U4.5 (Z0), U4.6 (~E), U4.7 (VEE), U4.8 (VSS)
M2: J1.38 (PHI2), U2.25 (A8)
NT_A10: J1.22 (VA10), U2.42 (A13)
unnamed: J1.36 (VCC), Q1.3 (D)
unnamed: J1.54 (EXP6), J2.2 (TIP), J2.3 (RING), J2.10 (TIP_SWITCH), J2.11 (RING_SWITCH)
unnamed: J3.2, J4.2, J5.2, J6.2, R2.2, U4.1 (Y1)
unnamed: J3.3, J4.3, J5.3, J6.3, R3.2, U4.13 (X1)
unnamed: J3.4, U3.5 (Y1)
unnamed: J3.6, U3.2 (Y2)
unnamed: J3.7, U3.4 (Y3)
unnamed: J4.4, U3.14 (X1)
unnamed: J4.6, U3.15 (X2)
unnamed: J4.7, U3.11 (X3)
unnamed: J5.4, U1.5 (Y1)
unnamed: J5.6, U1.2 (Y2)
unnamed: J5.7, U1.4 (Y3)
unnamed: J6.4, U1.14 (X1)
unnamed: J6.6, U1.15 (X2)
unnamed: J6.7, U1.11 (X3)
unnamed: JP1.2, U1.13 (X), U2.24 (B15)
unnamed: JP2.2, U1.3 (Y), U2.23 (B14)
unnamed: JP3.2, U2.22 (B13), U3.13 (X)
unnamed: JP4.2, U2.21 (B12), U3.3 (Y)
unnamed: Q1.1 (G), U4.4 (Z)
unnamed: R1.1, U2.40 (3V3)
unnamed: R1.2, U2.2 (C13), U4.9 (C), U4.10 (B), U4.11 (A)
unnamed: U1.9 (A1), U2.4 (C15), U3.9 (A1)
unnamed: U1.10 (A0), U2.3 (C14), U3.10 (A0)
unnamed: U2.36 (B8), U4.15 (Y)
unnamed: U2.37 (B9), U4.14 (X)
R/W: J1.14 (R/~W), U2.26 (A9)
VCC: C1.1, J3.5, J4.5, J5.5, J6.5, Q1.2 (S), R2.1, R3.1, U1.16 (Vdd), U2.38 (5V), U3.16 (Vdd), U4.3 (Z0), U4.16 (VDD)
~IRQ: J1.15 (~IRQ), U2.27 (A10)
~RD: J1.21 (~R), U2.43 (A14)
~ROMSEL: J1.50 (~PRG), U2.12 (A7)
~WR: J1.56 (~W), U2.30 (A15)

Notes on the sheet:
USB-NES-02
PAD STROBE
PAD CLOCK
BRAD TAYLOR COPYRIGHT 2018-2023 BTTD GROUP 02/16/2023

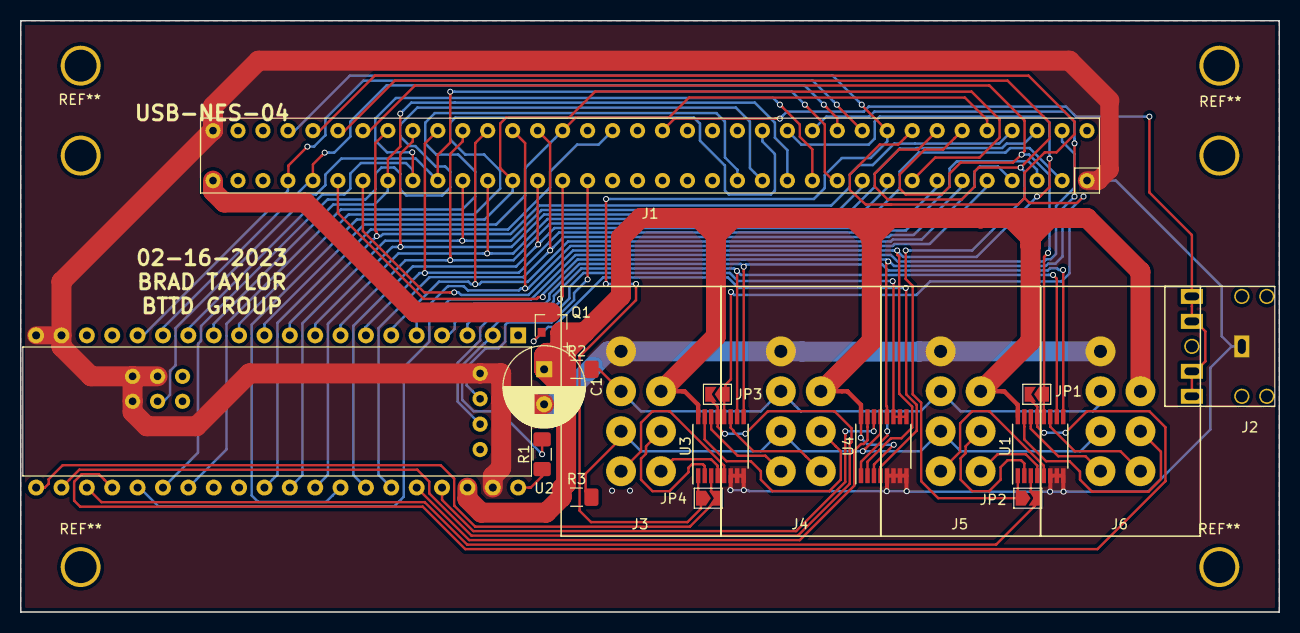
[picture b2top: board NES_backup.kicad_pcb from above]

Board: 2 copper layers, 126.0 x 59.2 mm, 19 parts (0 on the bottom side), 59 nets.

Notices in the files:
readme.md:
License:
Copywritten works, such as technical manuals and source code included in this repository are for educational and preservational "fair use" purposes only.  No copyright infringement is implied, solicited nor intended with the inclusion of these copywritten works for the Open-Source USB-NES Project.
The rest of the work in this archive, including any BTTD Group or Brad Taylor properties, is licensed under a Creative Commons Attribution-ShareAlike 4.0 International License.
http://creativecommons.org/licenses/by-sa/4.0
